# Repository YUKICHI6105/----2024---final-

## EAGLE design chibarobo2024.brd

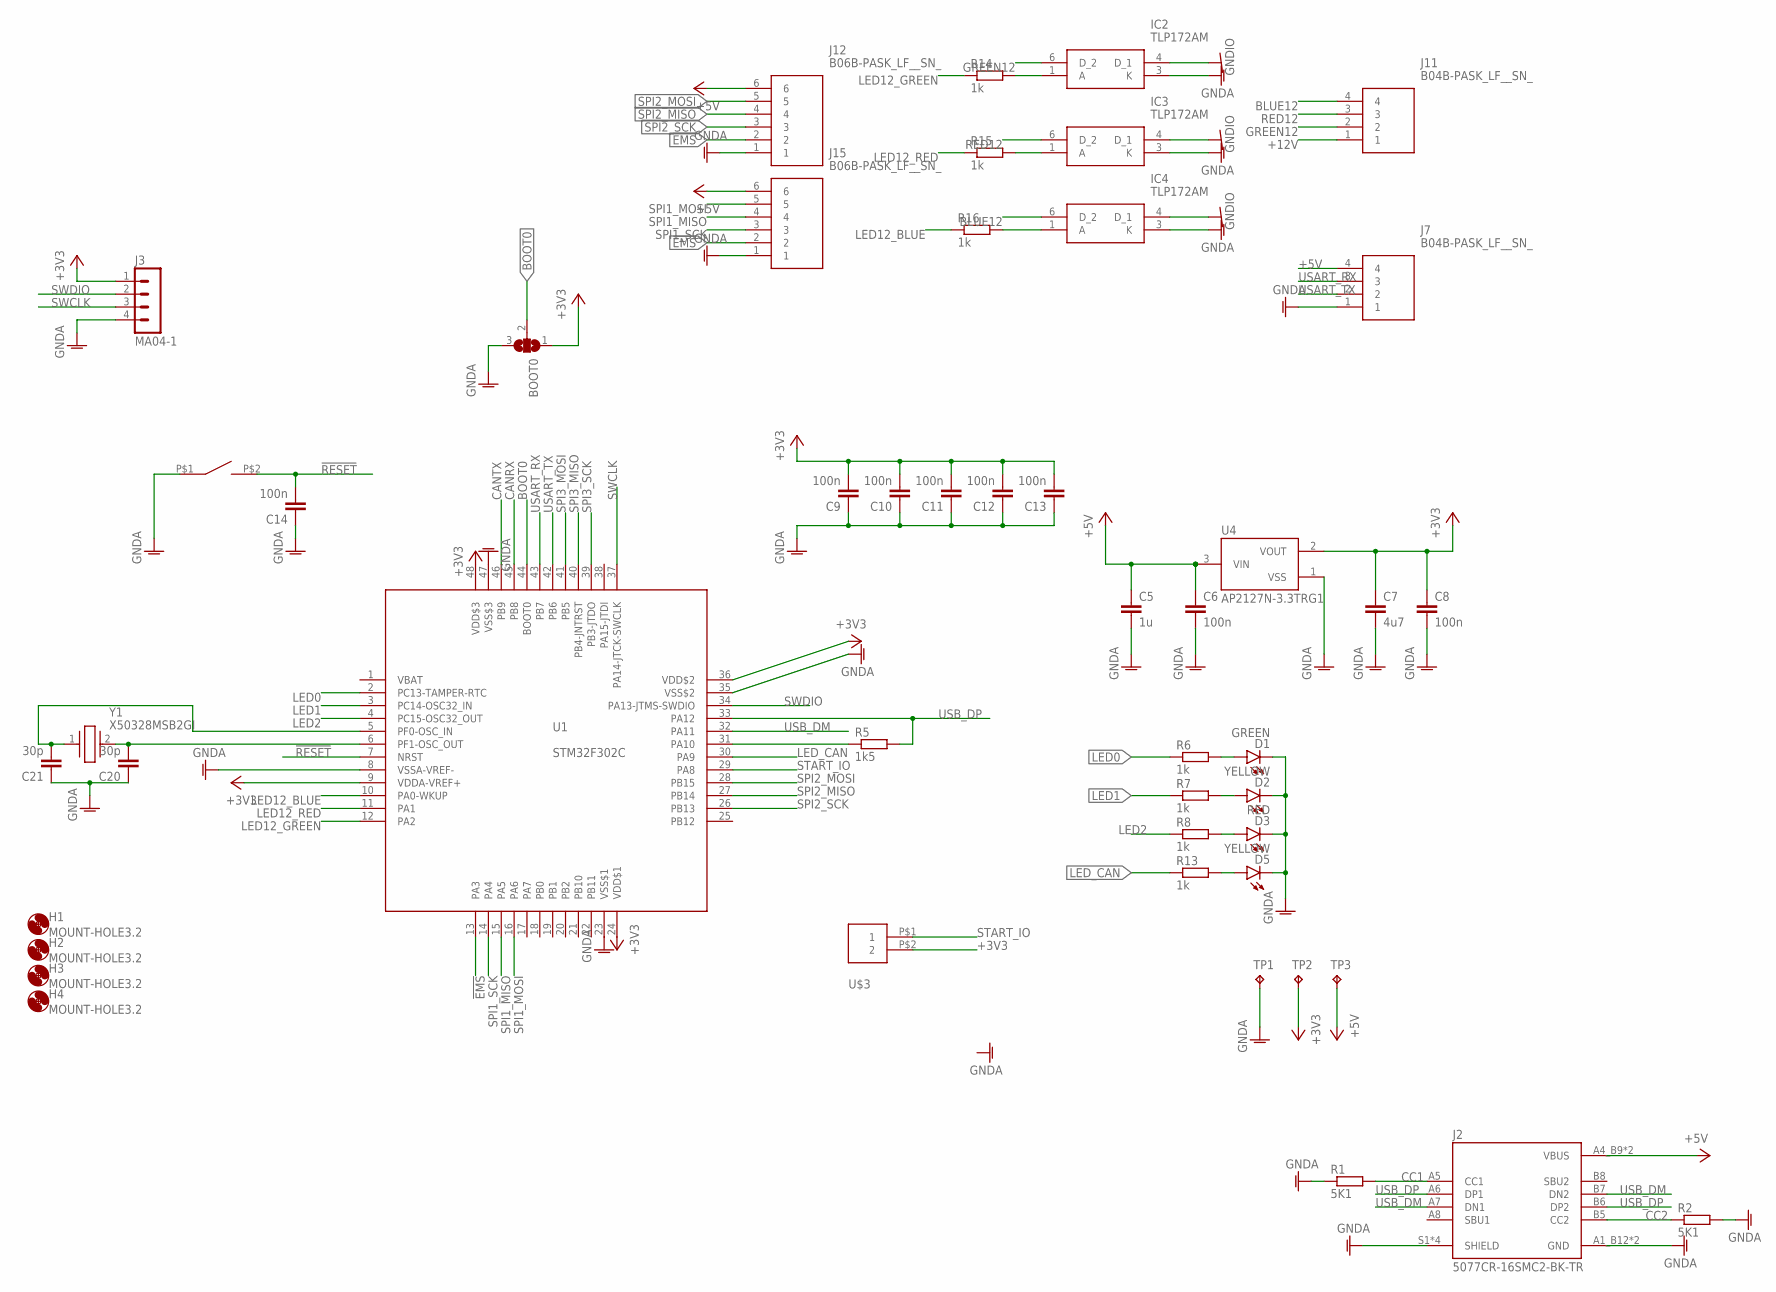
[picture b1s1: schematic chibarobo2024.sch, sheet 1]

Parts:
BOOT0: SJ2W; SJ_2
C5: 1u; C0603
C6, C8, C9, C10, C11, C12, C13, C14: 100n; C0603
C7: 4u7; C0805
C20, C21: 30p; C0603
D1: GREEN; CHIPLED_0805
D2, D5: YELLOW; CHIPLED_0805
D3: RED; CHIPLED_0805
H1, H2, H3, H4: MOUNT-HOLE3.2; 3,2
IC2, IC3, IC4: TLP172AM; 11-4M1S
J2: 5077CR-16SMC2-BK-TR; NELTRON_5077CR-16SMC2-BK-TR
J3: MA04-1
J7, J11: B04B-PASK_LF__SN_; B04BPASKLFSN
J12, J15: B06B-PASK_LF__SN_; B06BPASKLFSN
R1, R2: 5K1; R0603
R5: 1k5; R0603
R6, R7, R8, R13, R14, R15, R16: 1k; R0603
S1: SWITCH_TACTILETOP; SWITCH_TACTILE_3X6
TP1, TP2, TP3: TPB1,27; B1,27
U1: STM32F302C; LQFP48
U4: AP2127N-3.3TRG1; SOT95P240X110-3
U$3: XH-2-STRAIGHT; CON-XH-2-STRAIGHT
Y1: X50328MSB2GI; RESC5032X135N

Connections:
!EMS: J12.2, J15.2, U1.13 (PA3); also elsewhere on the board
!RESET: C14.2, S1.P$2 (2), U1.7 (NRST)
+3V3: BOOT0.1, C7.1, C8.1, C9.2, C10.2, C11.2, C12.2, C13.2, J3.1, TP2.TP, U1.9 (VDDA-VREF+), U1.24 (VDD$1), U1.36 (VDD$2), U1.48 (VDD$3), U4.2 (VOUT), U$3.P$2 (2); also elsewhere on the board
+5V: C5.1, C6.1, J2.A4_B9 (VBUS), J2.B4_A9 (VBUS), J7.4, J12.6, J15.6, TP3.TP, U4.3 (VIN); also elsewhere on the board
+12V: J11.1; also elsewhere on the board
BLUE12: IC4.6 (D_2), J11.4
BOOT0: BOOT0.2, U1.44 (BOOT0)
CANRX: U1.45 (PB8); also elsewhere on the board
CANTX: U1.46 (PB9); also elsewhere on the board
CC1: J2.A5 (CC1), R1.2
CC2: J2.B5 (CC2), R2.1
GNDA: BOOT0.3, C5.2, C6.2, C7.2, C8.2, C9.1, C10.1, C11.1, C12.1, C13.1, C14.1, C20.1, C21.1, D1.C, D2.C, D3.C, D5.C, IC2.3 (K), IC3.3 (K), IC4.3 (K), J2.A1_B12 (GND), J2.B1_A12 (GND), J2.S1 (SHIELD), J2.S2 (SHIELD), J2.S3 (SHIELD), J2.S4 (SHIELD), J3.4, J7.1, J12.1, J15.1, R1.1, R2.2, S1.P$1 (1), TP1.TP, U1.8 (VSSA-VREF-), U1.23 (VSS$1), U1.35 (VSS$2), U1.47 (VSS$3), U4.1 (VSS); also elsewhere on the board
GNDIO: IC2.4 (D_1), IC3.4 (D_1), IC4.4 (D_1); also elsewhere on the board
GREEN12: IC2.6 (D_2), J11.2
LED0: R6.1, U1.2 (PC13-TAMPER-RTC)
LED1: R7.1, U1.3 (PC14-OSC32_IN)
LED2: R8.1, U1.4 (PC15-OSC32_OUT)
LED12_BLUE: R16.1, U1.10 (PA0-WKUP)
LED12_GREEN: R14.1, U1.12 (PA2)
LED12_RED: R15.1, U1.11 (PA1)
LED_CAN: R13.1, U1.30 (PA9)
unnamed: D2.A, R7.2
unnamed: D1.A, R6.2
unnamed: C20.2, U1.6 (PF1-OSC_OUT), Y1.2
unnamed: C21.2, U1.5 (PF0-OSC_IN), Y1.1
unnamed: R5.1, U1.31 (PA10)
unnamed: D5.A, R13.2
unnamed: IC2.1 (A), R14.2
unnamed: IC3.1 (A), R15.2
unnamed: IC4.1 (A), R16.2
unnamed: D3.A, R8.2
RED12: IC3.6 (D_2), J11.3
SPI1_MISO: J15.4, U1.15 (PA5)
SPI1_MOSI: J15.5, U1.16 (PA6)
SPI1_SCK: J15.3, U1.14 (PA4)
SPI2_MISO: J12.4, U1.27 (PB14)
SPI2_MOSI: J12.5, U1.28 (PB15)
SPI2_SCK: J12.3, U1.26 (PB13)
SPI3_MISO: U1.40 (PB4-JNTRST)
SPI3_MOSI: U1.41 (PB5)
SPI3_SCK: U1.39 (PB3-JTDO)
START_IO: U1.29 (PA8), U$3.P$1 (1)
SWCLK: J3.3, U1.37 (PA14-JTCK-SWCLK)
SWDIO: J3.2, U1.34 (PA13-JTMS-SWDIO)
USART_RX: J7.3, U1.43 (PB7)
USART_TX: J7.2, U1.42 (PB6)
USB_DM: J2.A7 (DN1), J2.B7 (DN2), U1.32 (PA11)
USB_DP: J2.A6 (DP1), J2.B6 (DP2), R5.2, U1.33 (PA12)

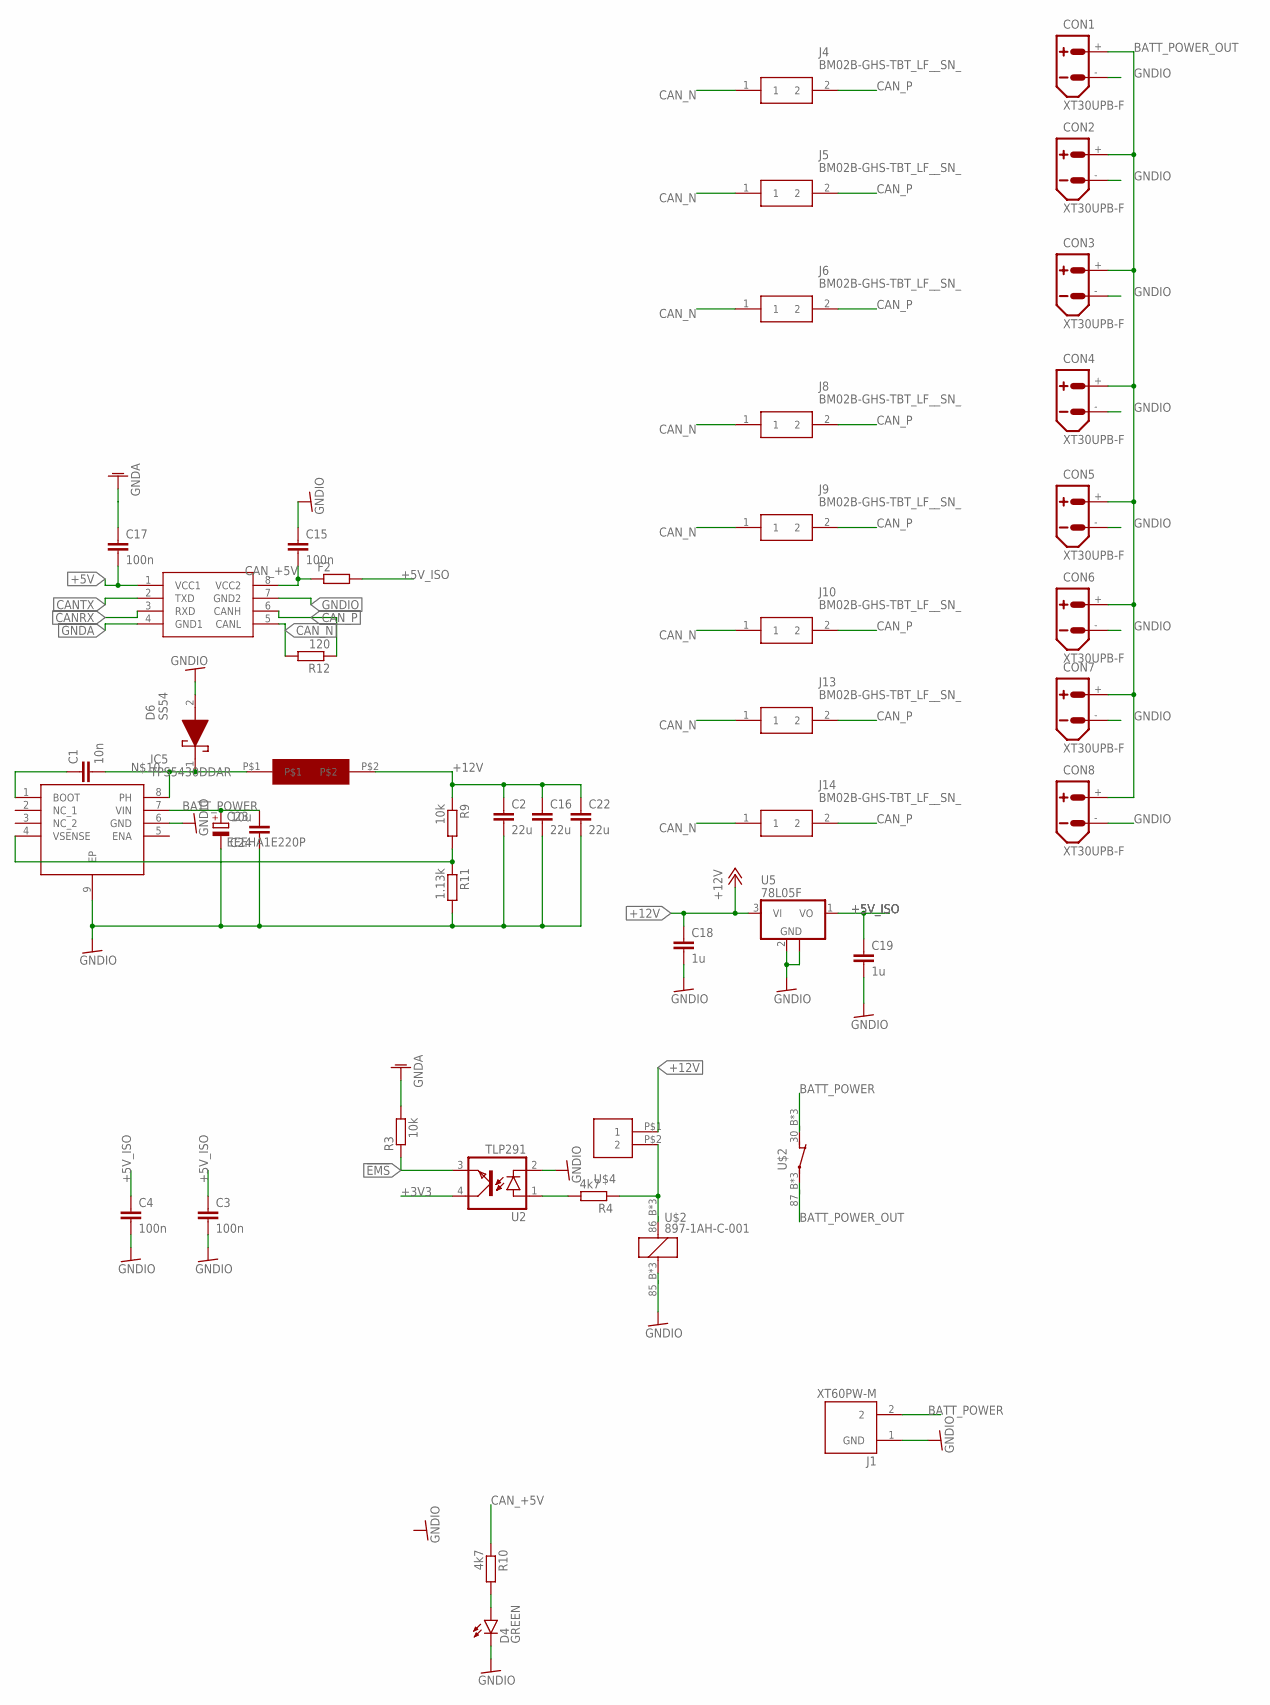
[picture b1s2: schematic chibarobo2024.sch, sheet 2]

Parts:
C1: 10n; C0603
C2, C16, C22: 22u; C0805
C3, C4, C15, C17: 100n; C0603
C18, C19: 1u; C0603
C23: EEEHA1E220P; 153CLV-0605
C24: 10u; C1210
CON1, CON2, CON3, CON4, CON5, CON6, CON7, CON8: XT30UPB-F
D4: GREEN; CHIPLED_0805
D6: SS54; DIOM5126X245N
F2: R-EU_R1206; R1206
IC5: TPS5430DDAR; SOIC127P600X170-9N
J1: XT60PW-M; AMASS_XT60PW-M
J4, J5, J6, J8, J9, J10, J13, J14: BM02B-GHS-TBT_LF__SN_; BM02B-GHS-TBT_1
R3, R9: 10k; R0603
R4, R10: 4k7; R0603
R11: 1.13k; R0603
R12: 120; R0603
U2: TLP291; MINI-FLAT-4
U5: 78L05F; SOT89
U$1: CA-IS1044S; SOIC8
U$2: 897-1AH-C-001
U$4: XH-2-STRAIGHT; CON-XH-2-STRAIGHT
U$5: INDUCTOR125_125

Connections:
!EMS: R3.1, U2.3 (EMIT); also elsewhere on the board
+3V3: U2.4 (COL); also elsewhere on the board
+5V: C17.2, U$1.1 (VCC1); also elsewhere on the board
+5V_ISO: C3.1, C4.1, C19.1, F2.2, U5.1 (VO)
+12V: C2.1, C16.1, C18.1, C22.1, R9.1, U5.3 (VI), U$4.P$1 (1), U$5.P$2; also elsewhere on the board
BATT_POWER: C23.+, C24.2, IC5.7 (VIN), J1.2, U$2.30_B (O), U$2.30_T (O), U$2.P$3 (O)
BATT_POWER_OUT: CON1.+, CON2.+, CON3.+, CON4.+, CON5.+, CON6.+, CON7.+, CON8.+, U$2.87_B, U$2.87_T, U$2.P$1
CANRX: U$1.3 (RXD); also elsewhere on the board
CANTX: U$1.2 (TXD); also elsewhere on the board
CAN_+5V: C15.2, F2.1, R10.1, U$1.8 (VCC2)
CAN_N: J4.1, J5.1, J6.1, J8.1, J9.1, J10.1, J13.1, J14.1, R12.2, U$1.5 (CANL)
CAN_P: J4.2, J5.2, J6.2, J8.2, J9.2, J10.2, J13.2, J14.2, R12.1, U$1.6 (CANH)
GNDA: C17.1, R3.2, U$1.4 (GND1); also elsewhere on the board
GNDIO: C2.2, C3.2, C4.2, C15.1, C16.2, C18.2, C19.2, C22.2, C23.-, C24.1, CON1.-, CON2.-, CON3.-, CON4.-, CON5.-, CON6.-, CON7.-, CON8.-, D4.C, D6.2 (A), IC5.6 (GND), IC5.9 (EP), J1.1 (GND), R11.2, U2.2 (C), U5.2 (GND), U5.2@1 (GND), U$1.7 (GND2), U$2.85_B (2), U$2.85_T (2), U$2.P$2 (2); also elsewhere on the board
unnamed: R4.1, U$2.86_B (1), U$2.86_T (1), U$2.P$4 (1), U$4.P$2 (2)
unnamed: R4.2, U2.1 (A)
unnamed: IC5.4 (VSENSE), R9.2, R11.1
unnamed: C1.1, IC5.1 (BOOT)
unnamed: D4.A, R10.2
unnamed: C1.2, D6.1 (K), IC5.8 (PH), U$5.P$1

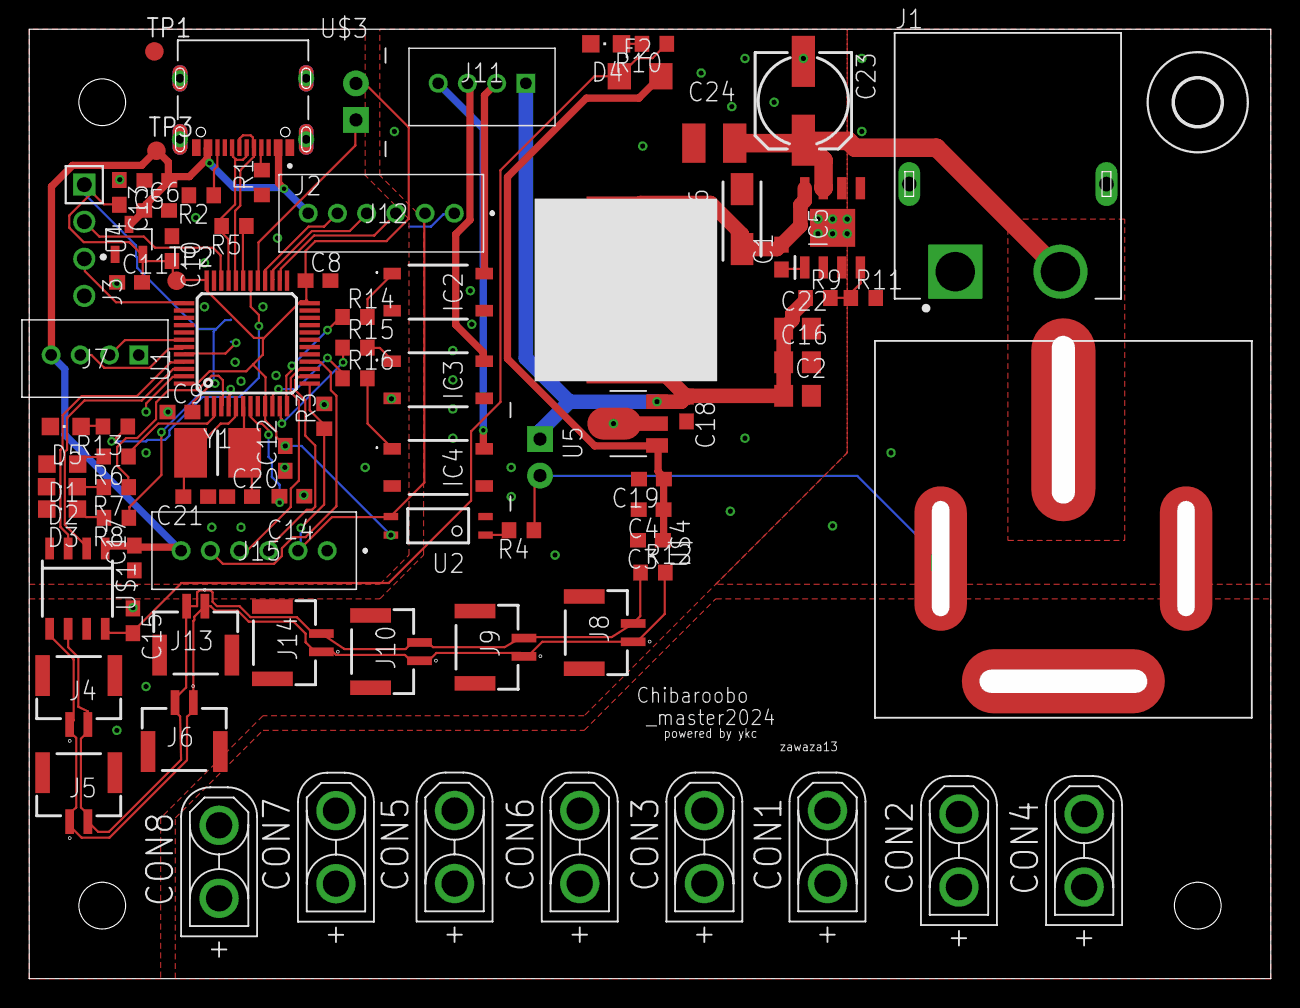
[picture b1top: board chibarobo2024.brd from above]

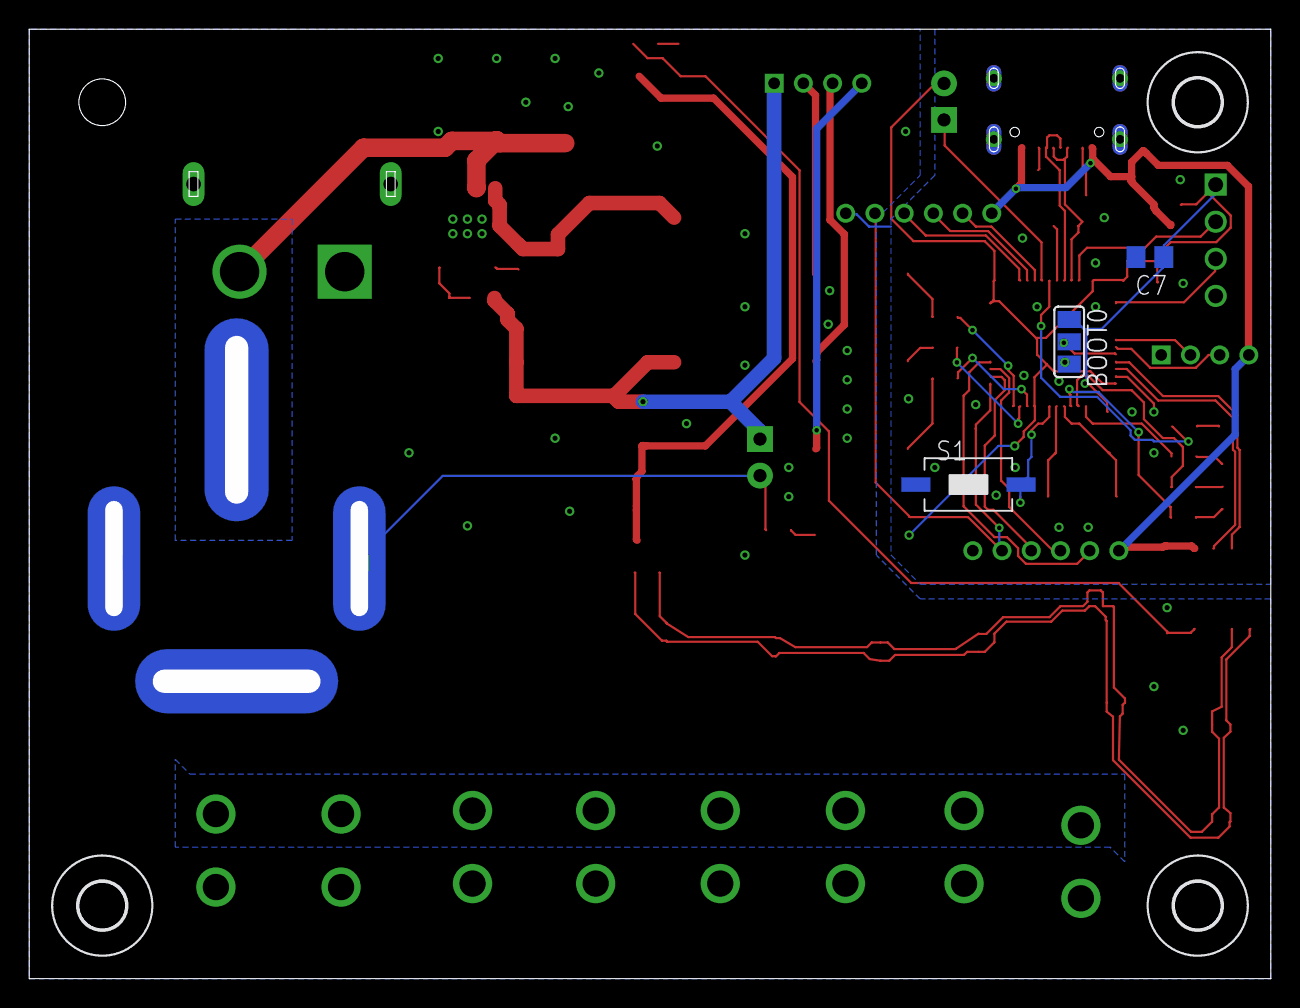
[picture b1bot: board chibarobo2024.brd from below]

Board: 2 copper layers, 83.4 x 63.4 mm, 93 parts (6 on the bottom side), 57 nets.

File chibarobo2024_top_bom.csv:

Comment,Designator,Footprint,LCSC Part #
1.13k,R11,R0603,
1k,R6 R7 R8 R13 R14 R15 R16,R0603,
1k5,R5,R0603,
1u,C5 C18 C19,C0603,
4k7,R4 R10,R0603,
5K1,R1 R2,R0603,
10k,R3 R9,R0603,
10n,C1,C0603,
10u,C24,C1210,
22u,C2 C16 C22,C0805,
30p,C20 C21,C0603,
78L05F,U5,SOT89,
100n,C3 C4 C6 C8 C9 C10 C11 C12 C13 C14 C15 C17,C0603,
120,R12,R0603,
897-1AH-C-001,U$2,897-1AH-C-001,
5077CR-16SMC2-BK-TR,J2,NELTRON_5077CR-16SMC2-BK-TR,
AP2127N-3.3TRG1,U4,SOT95P240X110-3,C5446
BM02B-GHS-TBT_LF__SN_,J4 J5 J6 J8 J9 J10 J13 J14,BM02B-GHS-TBT_1,
CA-IS1044S,U$1,SOIC8,
EEEHA1E220P,C23,153CLV-0605,
GREEN,D1 D4,CHIPLED_0805,C2297
INDUCTOR125_125,U$5,INDUCTOR125_125,
RED,D3,CHIPLED_0805,C2286
SS54,D6,DIONM7959X262N,
STM32F302C,U1,LQFP48,
TLP172AM,IC2 IC3 IC4,11-4M1S,
TLP291,U2,MINI-FLAT-4,
TPB1 27,TP1,B1 27,
TPB1 27,TP2,B1 27,
TPB1 27,TP3,B1 27,
TPS5430DDAR,IC5,SOIC127P600X170-9N,
X50328MSB2GI,Y1,RESC5032X135N,
YELLOW,D2 D5,CHIPLED_0805,C72038
fuse,F2,,
